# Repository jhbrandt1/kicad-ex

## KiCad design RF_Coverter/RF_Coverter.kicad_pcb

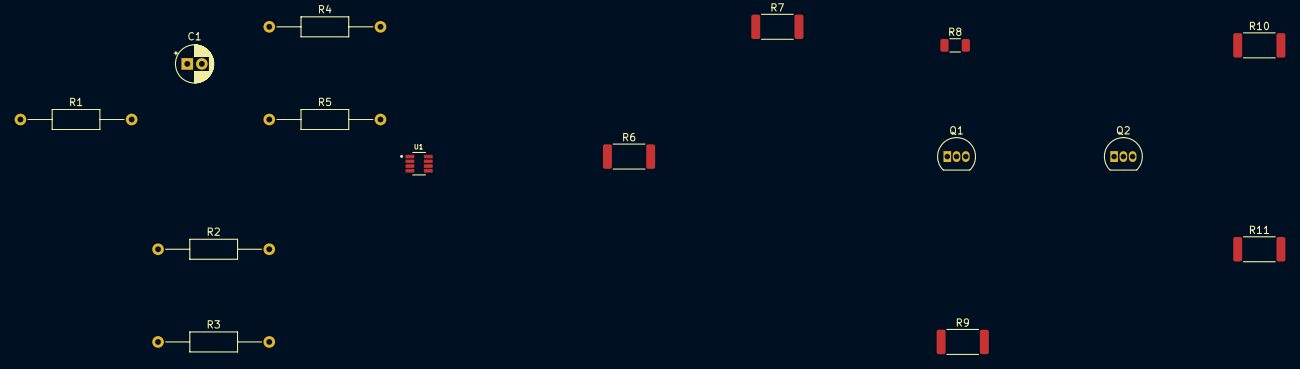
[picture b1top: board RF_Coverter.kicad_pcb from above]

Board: 2 copper layers, 15 parts (0 on the bottom side), 10 nets, no tracks yet.

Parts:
C1: 0.1u; CP_Radial_D5.0mm_P2.00mm
Q1: 2N3906; TO-92_Inline
Q2: 2N3904; TO-92_Inline
R1: 50; R_Axial_DIN0207_L6.3mm_D2.5mm_P15.24mm_Horizontal
R2, R3, R4, R5: 2k; R_Axial_DIN0207_L6.3mm_D2.5mm_P15.24mm_Horizontal
R6, R9, R11: 100; R_2512_6332Metric
R7: 5.1k; R_2512_6332Metric
R8: 160; R_1206_3216Metric
R10: 10k; R_2512_6332Metric
U1: MAX9203EKAT; SOT65P280X145-8N

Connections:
+5V: R3.1, R4.1, R7.1, U1.1 (VDD), U1.4 (LATCH), U1.8 (VCC)
-1V: R8.1, R10.1
GND: R1.2, R2.2, R5.2, R11.2, U1.3 (GND), U1.5 (VEE)
unnamed: Q1.2 (B), R6.2, R7.2
unnamed: Q1.3 (C), Q2.1 (E), R8.2
unnamed: Q1.1 (E), R9.1
unnamed: Q2.2 (B), R10.2, R11.1
unnamed: C1.2, R4.2, R5.1, U1.7 (IN+)
unnamed: R2.1, R3.2, U1.6 (IN-)
Sine_Wave: C1.1, R1.1

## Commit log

2023-09-08 RF converter
    All files
